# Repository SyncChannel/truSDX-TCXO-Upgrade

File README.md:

# truSDX-TCXO-Upgrade
TCXO upgrade for the (tr)uSDX HF radio

Please see the OSHPark project page for more information:

https://oshpark.com/shared_projects/4DRo2NCn

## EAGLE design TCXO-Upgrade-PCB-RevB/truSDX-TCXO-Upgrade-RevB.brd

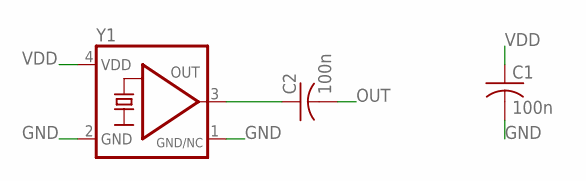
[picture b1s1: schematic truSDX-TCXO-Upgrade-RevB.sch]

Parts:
C1, C2: 100n; C0603
Y1: KXO-TCXO-CMOS-84; 3.2X2.5_KXO-84-TCXO

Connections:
GND: C1.2, Y1.1 (GND/NC), Y1.2 (GND)
unnamed: C2.1, Y1.3 (OUT)
OUT: C2.2
VDD: C1.1, Y1.4 (VDD)

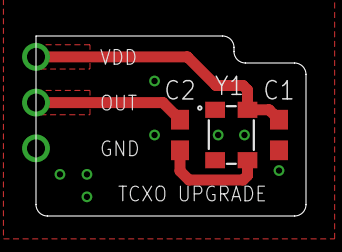
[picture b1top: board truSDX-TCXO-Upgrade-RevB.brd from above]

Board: 2 copper layers, 15.0 x 10.0 mm, 3 parts (0 on the bottom side), 3 nets.

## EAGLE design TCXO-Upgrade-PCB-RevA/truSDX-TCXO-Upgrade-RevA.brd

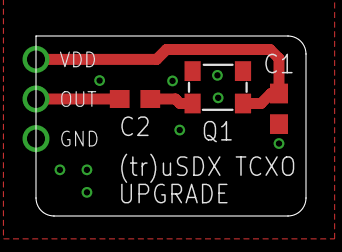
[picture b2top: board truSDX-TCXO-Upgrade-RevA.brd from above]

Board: 2 copper layers, 15.0 x 10.0 mm, 3 parts (0 on the bottom side), 3 nets.

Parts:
C1, C2: 100n; C0603
Q1: 3.2X2.5_KXO-84-TCXO

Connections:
GND: C1.2, Q1.1, Q1.2
unnamed: C2.1, Q1.3
VDD: C1.1, Q1.4

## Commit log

2022-08-14 Create LICENSE
2022-08-14 Create test

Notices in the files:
parts and their libraries:
crystal-geyer_V1_0: Copyright: Geyer-Electronic
